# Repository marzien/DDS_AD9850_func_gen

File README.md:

# AD9850 DDS Function Generator (STM32F103)

Rotary-encoder controlled signal generator built from an AD9850 DDS module,
a 20x4 HD44780 LCD with PCF8574 I2C backpack and an STM32F103RB.

## Features
- 0 Hz – 40 MHz, 1 Hz resolution (125 MHz reference clock)
- STM32 runs at 72 MHz (8 MHz crystal × 9, APB1 36 MHz, 48 MHz USB clock)
- FreeRTOS V11.2.0 with four statically allocated tasks (no heap)
- Phase offset in 11.25° steps
- Output on/off (AD9850 power-down)
- Linear frequency sweep (up or down), period 0.1 s – 60 s
- Burst / gated output: on for X ms, off for Y ms (1 ms – 60 s each), also during a sweep
- Settings are saved to flash and restored at power-up
- Text command interface over the Blue Pill micro-USB port (USB virtual COM port)
- Outputs of the AD9850 module: **sine** on ZOUT1/ZOUT2, **square** on QOUT1/QOUT2
  (square duty cycle is set by the blue trimmer on the module). The AD9850 cannot
  generate triangle/sawtooth.

## Wiring
| STM32 | Function | Connect to |
|------|----------|------------|
| PA0  | W_CLK    | AD9850 W_CLK |
| PA1  | FQ_UD    | AD9850 FQ_UD |
| PA2  | Data     | AD9850 D7 (serial data) |
| –    | RESET    | AD9850 RESET → GND |
| PA6  | BTN_A    | Encoder A / CLK |
| PA4  | BTN_B    | Encoder B / DT |
| PA5  | BTN_PUSH | Encoder SW (to GND when pressed; internal pull-up + optional 10k to 3V3) |
| PB10 | I2C2 SCL | LCD backpack SCL |
| PB11 | I2C2 SDA | LCD backpack SDA |

Power the encoder from 3V3 (PA4/PA5/PA6 are not 5 V tolerant).
LCD address 0x27 or 0x3F is auto-detected (`SLAVE_ADDRESS_LCD` in `I2C_LCD.h`).

## Controls
**Main screen**
```
Freq:      1,000 Hz     <- cursor under the digit being changed
Step: 1 kHz
Phase: 0.00°
Output: ON
```
- Rotate: change frequency by the digit under the cursor
- Press and turn: change the step – clockwise = bigger, counter-clockwise = smaller
  (1 Hz … 10 MHz, shown on the "Step:" line and by the cursor)
- Short press: move cursor one digit left (1 Hz … 10 MHz, wraps)
- Long press: open menu
- While sweeping the screen shows live frequency, start, stop and period;
  short press stops the sweep

**Menu** (3 items visible, scrolls)
```
MENU      hold=exit
>Output           ON
 Phase         0.00°
 Sweep           OFF
```
Items: Output, Phase, Burst, On time, Off time, Sweep, Sw start, Sw stop, Sw time, Exit
- Rotate: select item / change value while editing (marker changes to `*`)
- Short press: edit / confirm (on frequency items it moves the digit cursor)
- Press and turn while editing Sw start / Sw stop: change the step
- Long press: confirm edit, or leave the menu

**Burst:** set Burst ON, then On time / Off time. The output is switched with the
AD9850 power-down bit, timed from SysTick (1 ms resolution). Each cycle starts with
the on time. Times change in 1 ms steps below 100 ms, 10 ms below 1 s, 100 ms below
10 s and 1 s above. The main screen shows `Burst on/off ms` on the last line (`Out:BST`
while sweeping). Gating is not synchronised to the waveform, so a burst does not start
or end at a zero crossing.

## Saved settings
All settings (frequency, step, phase, output, sweep start/stop/time, sweep on/off)
are saved to flash automatically 3 s after the last knob or button action, and
restored at power-up. Hold the encoder button while powering up to restore the
defaults (the splash screen shows "Defaults restored").

Storage uses the last 1 KB page of the first 64 KB (0x0800FC00), split into
32 slots, so the page is erased only once per 32 saves. For that reason the
linker script limits program flash to 63 KB.

LCD size is set by `LCD_COLS` / `LCD_ROWS` in `Core/Inc/I2C_LCD.h` (layout is designed for 20x4).

## USB command interface
Plug the Blue Pill micro-USB into a PC: it appears as a virtual COM port
("AD9850 DDS Function Generator", VID 0483 / PID 5740; Windows 10/11 needs no driver).
Open it with any terminal (PuTTY, Arduino serial monitor, Python `pyserial`); the baud rate
does not matter. One command per line, case-insensitive; every command answers `OK` or `ERR ...`.

| Command | Meaning |
|---|---|
| `F 1000`, `F 12.5k`, `F 7.1M` | set frequency (0 … 40 MHz), stops a running sweep |
| `STEP 1k` | encoder step, power of ten 1 … 10M |
| `PH 90` | phase in degrees (rounded to 11.25° steps) |
| `OUT ON` / `OUT OFF` | output on/off |
| `SWEEP 100 10k 2.5` | sweep 100 Hz → 10 kHz in 2.5 s and start it |
| `SWEEP ON` / `SWEEP OFF` | start/stop the sweep with the stored settings |
| `BURST 10 90` | burst: 10 ms on, 90 ms off, and start it |
| `BURST ON` / `BURST OFF` | burst mode on/off |
| `SAVE` | write settings to flash now (otherwise saved 3 s after the last change) |
| `?` or `STATUS` | print all settings |
| `*IDN?` | identification string |
| `MEM` | flash / RAM use and the minimum free stack of every task |
| `HELP` | list the commands |

Remote changes update the LCD and are autosaved like changes made with the knob.
Notes:
- Some Blue Pills have a 10 kΩ resistor (R10) on USB D+ instead of 1.5 kΩ. If the PC does
  not detect the board, add 1.8 kΩ between PA12 and 3.3 V (or replace R10 with 1.5 kΩ).
- The firmware pulls D+ low for 20 ms at start-up so the PC re-detects the board after a reset.
- With the carrier PCB, do not connect the PC USB and the 5 V DC jack at the same time
  (the PC would supply the whole board through the Blue Pill 5V pin).

## Firmware structure (FreeRTOS)
| Task | Priority | Stack | Job |
|---|---|---|---|
| DDS | 4 (highest) | 640 B | the only code that writes to the AD9850: applies settings, steps the sweep every 5 ms, runs the burst gate every 1 ms |
| INPUT | 3 | 512 B | samples the encoder and button every 1 ms, wakes the UI task |
| UI | 2 | 1536 B | menus, LCD, settings autosave to flash |
| USB | 1 | 1536 B | command parser, woken by the USB interrupt |
| IDLE | 0 | 384 B | FreeRTOS idle task |

- The UI and USB tasks share the settings under one mutex and hand them to the DDS task with
  `DDS_Configure()`. Because the DDS task has the highest priority, sweep and burst timing no
  longer depend on LCD redraws or USB traffic.
- FreeRTOS uses SysTick; the HAL time base runs on TIM4. The USB interrupt has priority 5
  (`configLIBRARY_MAX_SYSCALL_INTERRUPT_PRIORITY`), TIM4 / SysTick / PendSV priority 15.
- Everything is statically allocated (`configSUPPORT_DYNAMIC_ALLOCATION 0`), so RAM use is fixed
  at link time. Stack overflow checking (method 2) is on.
- The Debug configuration is built with `-Og` (was `-O0`) to keep flash use low.

### Memory budget
`python tools/mem_check.py` (after a build) prints flash / RAM use and a worst-case stack
estimate for every task from the call graph:

| | Used | Limit |
|---|---|---|
| Flash | 39.3 KB | 63 KB (61 %) |
| RAM (data + bss + heap + main stack) | 12.2 KB | 20 KB (59 %) |

| Stack | Size | Estimated need |
|---|---|---|
| DDS | 640 B | 192 B |
| INPUT | 512 B | 136 B |
| UI | 1536 B | 760 B |
| USB | 1536 B | 704 B |
| IDLE | 384 B | 64 B |
| Interrupts (main stack) | 1536 B | 504 B |

These are estimates; the USB command `MEM` reports the real minimum free stack on the board.

## Tuning
In `Core/Inc/Rotary_Sw.h`:
- `RS_STEPS_PER_DETENT` – 4 for KY-040 style encoders, 2 if one click counts double
- `RS_REVERSE` – flip rotation direction
- `RS_BTN_ACTIVE_LEVEL` – 0 (default) for a switch to GND, 1 for a switch to 3V3

## Building (STM32CubeIDE)
- File > Import > General > Existing Projects into Workspace, select this folder
  (project name `DDS_AD9850_FULL`), then build with the hammer icon.
- Startup code: `Core/Startup/startup_stm32f103rbtx.s`, linker script: `STM32F103RBTX_FLASH.ld`.
- Pin configuration lives in `DDS_AD9850_FULL.ioc` (toolchain: STM32CubeIDE). Application code is
  inside `USER CODE` blocks and in separate files, so it survives code regeneration.

## Hardware
A KiCad carrier PCB (Blue Pill + AD9850 module sockets, level shifter, LM7171 sine amplifier,
square buffer, sync output, BNC connectors) is in [`Hardware/`](Hardware/README.md).

## Source layout
- `Core/Src/AD9850.c` – DDS serial driver
- `Core/Src/I2C_LCD.c` – LCD driver
- `Core/Src/Rotary_Sw.c` – encoder + button, polled by the INPUT task (1 ms)
- `Core/Src/App.c` – task creation, settings mutex, memory report, RTOS hooks
- `Core/Src/Dds.c` – DDS task: output, sweep and burst timing
- `Core/Src/FuncGen.c` – UI task: menus, LCD, settings
- `Core/Src/Flash_Store.c` – wear-levelled settings storage in flash
- `Core/Src/UsbCmd.c` – USB task: command parser
- `Core/Inc/FreeRTOSConfig.h` – kernel configuration
- `Middlewares/Third_Party/FreeRTOS/` – FreeRTOS kernel V11.2.0 (tasks, queue, list, ARM_CM3 port)
- `tools/mem_check.py` – flash / RAM / stack budget check
- `USB_DEVICE/` – USB CDC device glue (descriptors, low-level driver, virtual COM port)
- `Middlewares/ST/STM32_USB_Device_Library/` – ST USB device library v2.11.6 (core + CDC)

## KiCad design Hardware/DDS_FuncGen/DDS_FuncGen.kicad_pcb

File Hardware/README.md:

# Carrier PCB (KiCad 10)

100 × 90 mm, 2-layer board that carries the Blue Pill and the AD9850 module on
female headers, plus the output stage.

## What is on the board
- **Blue Pill** socket (2 × 1×20 female headers, rows 15.24 mm apart, USB towards the left edge).
- **AD9850 module (HC-SR08)** socket (2 × 1×10 female headers).
- **74AHCT125** level shifter: PA0/PA1/PA2/PA3 → W_CLK/FQ_UD/DATA/RESET. The STM32's 3.3 V
  logic is below the AD9850's 3.5 V input-high minimum at 5 V supply, so the buffer makes it reliable.
  RESET is driven by PA3; R1 keeps it low (the current firmware leaves PA3 as an input).
- Data row of the module: D2…D6 tied to GND (guarantees serial mode). VCC, D7 and GND
  of that row are deliberately **not connected**, because some modules have D7 and GND swapped.
- **Sine output (J4, BNC)**: ZOUT2 → 22 µF + 100 nF AC coupling (centres the sine on 0 V) →
  1 k amplitude pot RV1 → LM7171, gain 4 → 49.9 Ω → BNC.
- **Square output (J5, BNC)**: QOUT1 → 74LVC1G17 buffer → 68 Ω → BNC (0–5 V into high-Z).
- **Sync output (J6, BNC)**: PB0 → 100 Ω (needs the sync firmware feature).
- **Power**: 5 V DC jack (2.1 mm, centre +) → SS34 reverse protection → +5V.
  A0515S-2WR3 isolated DC-DC → LC filter → 78L12 / 79L12 → ±12 V for the LM7171.
- Headers: **J2** LCD (GND, VCC, SDA, SCL), **J3** KY-040 (CLK, DT, SW, +, GND), R8 = 10 k SW pull-up.
- 4 × M3 mounting holes.

## Check before ordering
1. **AD9850 module row spacing**: set to 20.32 mm (`AD9850_ROW_SPACING` in `tools/design.py`).
   The seller drawing says "20 mm" – measure your module.
2. **Blue Pill orientation**: with USB on the left, the top row must read
   `G G 3.3 R B11 B10 … A0 C15 C14 C13 VB`. The silkscreen shows every pin name – compare with your board.
3. Power the board from the DC jack **or** the Blue Pill USB, not from both at the same time.

## Files
| Path | Content |
|---|---|
| `DDS_FuncGen/DDS_FuncGen.kicad_pro` | KiCad project (open this) |
| `DDS_FuncGen/production/DDS_FuncGen_gerbers_JLCPCB.zip` | Gerbers + drill, ready to upload |
| `DDS_FuncGen/production/DDS_FuncGen_BOM.csv` | Bill of materials |
| `DDS_FuncGen/production/DDS_FuncGen_schematic.pdf` | Schematic |
| `DDS_FuncGen/production/erc.rpt`, `drc.rpt` | 0 ERC errors, 0 DRC violations, 0 unconnected |
| `tools/design.py` | Parts, nets and positions (single source) |
| `tools/gen_project.py` | Generates libraries, schematic and PCB from `design.py` |
| `tools/route.py` | Autoroutes with Freerouting and adds GND planes |

## Regenerating
```
"%LOCALAPPDATA%\Programs\KiCad\10.0\bin\python.exe" tools\gen_project.py
"%LOCALAPPDATA%\Programs\KiCad\10.0\bin\python.exe" tools\route.py <freerouting-2.1.0.jar> <java.exe>
```
`gen_project.py --sch-only` rewrites only the schematic and libraries, leaving the routed PCB alone.
Freerouting 2.1.0 runs on Java 21 (the JRE bundled with STM32CubeIDE works).

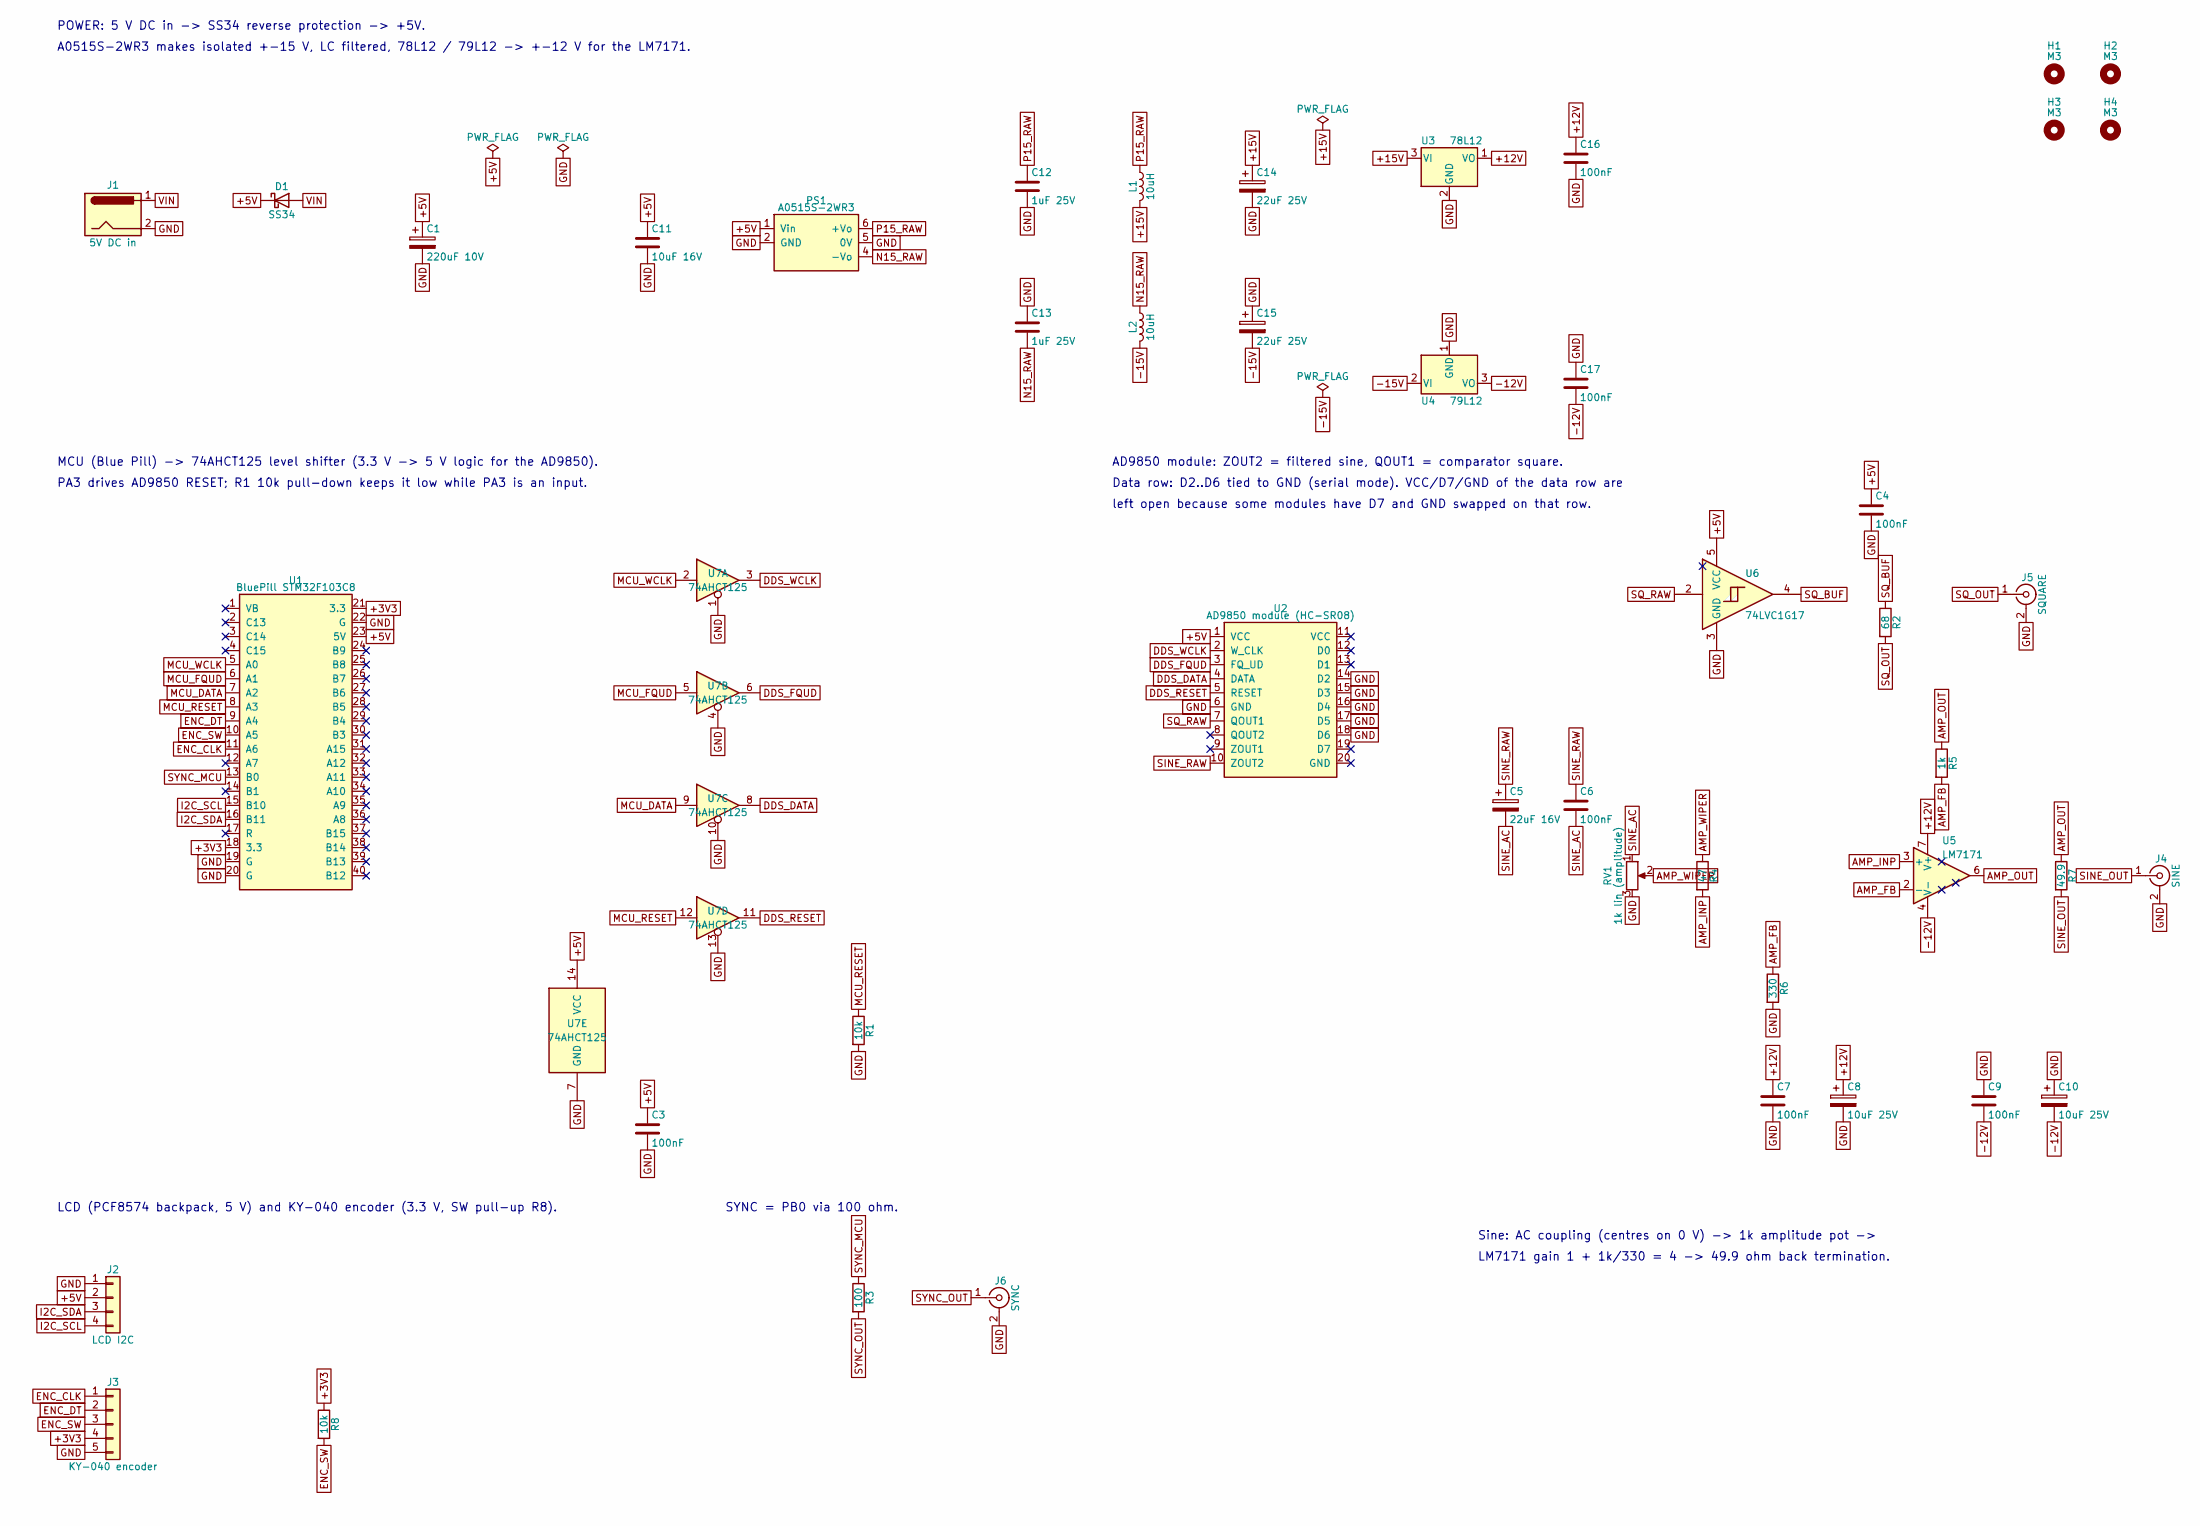
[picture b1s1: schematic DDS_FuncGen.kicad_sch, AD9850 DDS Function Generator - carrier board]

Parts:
C1: 220uF 10V; CP_Radial_D8.0mm_P3.50mm
C3, C4, C6, C7, C9, C16, C17: 100nF; C_0805_2012Metric_Pad1.18x1.45mm_HandSolder
C5: 22uF 16V; CP_Radial_D5.0mm_P2.00mm
C8, C10: 10uF 25V; CP_Radial_D5.0mm_P2.00mm
C11: 10uF 16V; C_0805_2012Metric_Pad1.18x1.45mm_HandSolder
C12, C13: 1uF 25V; C_0805_2012Metric_Pad1.18x1.45mm_HandSolder
C14, C15: 22uF 25V; CP_Radial_D5.0mm_P2.00mm
D1: SS34; D_SMA_Handsoldering
H1, H2, H3, H4: M3; MountingHole_3.2mm_M3
J1: 5V DC in; BarrelJack_Horizontal
J2: LCD I2C; PinHeader_1x04_P2.54mm_Vertical
J3: KY-040 encoder; PinHeader_1x05_P2.54mm_Vertical
J4: SINE; BNC_TEConnectivity_1478035_Horizontal
J5: SQUARE; BNC_TEConnectivity_1478035_Horizontal
J6: SYNC; BNC_TEConnectivity_1478035_Horizontal
L1, L2: 10uH; L_1210_3225Metric_Pad1.42x2.65mm_HandSolder
PS1: A0515S-2WR3; Mornsun_SIP6_A_S-2WR3
R1, R8: 10k; R_0805_2012Metric_Pad1.20x1.40mm_HandSolder
R2: 68; R_0805_2012Metric_Pad1.20x1.40mm_HandSolder
R3: 100; R_0805_2012Metric_Pad1.20x1.40mm_HandSolder
R4: 47; R_0805_2012Metric_Pad1.20x1.40mm_HandSolder
R5: 1k; R_0805_2012Metric_Pad1.20x1.40mm_HandSolder
R6: 330; R_0805_2012Metric_Pad1.20x1.40mm_HandSolder
R7: 49.9; R_0805_2012Metric_Pad1.20x1.40mm_HandSolder
RV1: 1k lin (amplitude); Potentiometer_Alps_RK09K_Single_Vertical
U1: BluePill STM32F103C8; BluePill_Socket
U2: AD9850 module (HC-SR08); AD9850_Module_Socket
U3: 78L12; TO-92_Inline
U4: 79L12; TO-92_Inline
U5: LM7171; SOIC-8_3.9x4.9mm_P1.27mm
U6: 74LVC1G17; SOT-23-5_HandSoldering
U7: 74AHCT125; SOIC-14_3.9x8.7mm_P1.27mm

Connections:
+3V3: J3.4, R8.1, U1.18 (3.3), U1.21 (3.3)
+5V: C1.1, C3.1, C4.1, C11.1, D1.1 (K), J2.2, PS1.1 (Vin), U1.23 (5V), U2.1 (VCC), U6.5 (VCC), U7.14 (VCC)
+12V: C7.1, C8.1, C16.1, U3.1 (VO), U5.7 (V+)
+15V: C14.1, L1.2, U3.3 (VI)
-12V: C9.2, C10.2, C17.2, U4.3 (VO), U5.4 (V-)
-15V: C15.2, L2.2, U4.2 (VI)
AMP_FB: R5.2, R6.1, U5.2 (-)
AMP_INP: R4.2, U5.3 (+)
AMP_OUT: R5.1, R7.1, U5.6
AMP_WIPER: R4.1, RV1.2
DDS_DATA: U2.4 (DATA), U7.8
DDS_FQUD: U2.3 (FQ_UD), U7.6
DDS_RESET: U2.5 (RESET), U7.11
DDS_WCLK: U2.2 (W_CLK), U7.3
ENC_CLK: J3.1, U1.11 (A6)
ENC_DT: J3.2, U1.9 (A4)
ENC_SW: J3.3, R8.2, U1.10 (A5)
GND: C1.2, C3.2, C4.2, C7.2, C8.2, C9.1, C10.1, C11.2, C12.2, C13.1, C14.2, C15.1, C16.2, C17.1, J1.2, J2.1, J3.5, J4.2 (Ext), J5.2 (Ext), J6.2 (Ext), PS1.2 (GND), PS1.5 (0V), R1.2, R6.2, RV1.3, U1.19 (G), U1.20 (G), U1.22 (G), U2.6 (GND), U2.14 (D2), U2.15 (D3), U2.16 (D4), U2.17 (D5), U2.18 (D6), U3.2 (GND), U4.1 (GND), U6.3 (GND), U7.1, U7.4, U7.7 (GND), U7.10, U7.13
I2C_SCL: J2.4, U1.15 (B10)
I2C_SDA: J2.3, U1.16 (B11)
MCU_DATA: U1.7 (A2), U7.9
MCU_FQUD: U1.6 (A1), U7.5
MCU_RESET: R1.1, U1.8 (A3), U7.12
MCU_WCLK: U1.5 (A0), U7.2
N15_RAW: C13.2, L2.1, PS1.4 (-Vo)
P15_RAW: C12.1, L1.1, PS1.6 (+Vo)
SINE_AC: C5.2, C6.2, RV1.1
SINE_OUT: J4.1 (In), R7.2
SINE_RAW: C5.1, C6.1, U2.10 (ZOUT2)
SQ_BUF: R2.1, U6.4
SQ_OUT: J5.1 (In), R2.2
SQ_RAW: U2.7 (QOUT1), U6.2
SYNC_MCU: R3.1, U1.13 (B0)
SYNC_OUT: J6.1 (In), R3.2
VIN: D1.2 (A), J1.1

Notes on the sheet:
POWER: 5 V DC in -> SS34 reverse protection -> +5V.
A0515S-2WR3 makes isolated +-15 V, LC filtered, 78L12 / 79L12 -> +-12 V for the LM7171.
MCU (Blue Pill) -> 74AHCT125 level shifter (3.3 V -> 5 V logic for the AD9850).
PA3 drives AD9850 RESET; R1 10k pull-down keeps it low while PA3 is an input.
AD9850 module: ZOUT2 = filtered sine, QOUT1 = comparator square.
Data row: D2..D6 tied to GND (serial mode). VCC/D7/GND of the data row are
left open because some modules have D7 and GND swapped on that row.
Sine: AC coupling (centres on 0 V) -> 1k amplitude pot ->
LM7171 gain 1 + 1k/330 = 4 -> 49.9 ohm back termination.
LCD (PCF8574 backpack, 5 V) and KY-040 encoder (3.3 V, SW pull-up R8).
SYNC = PB0 via 100 ohm.

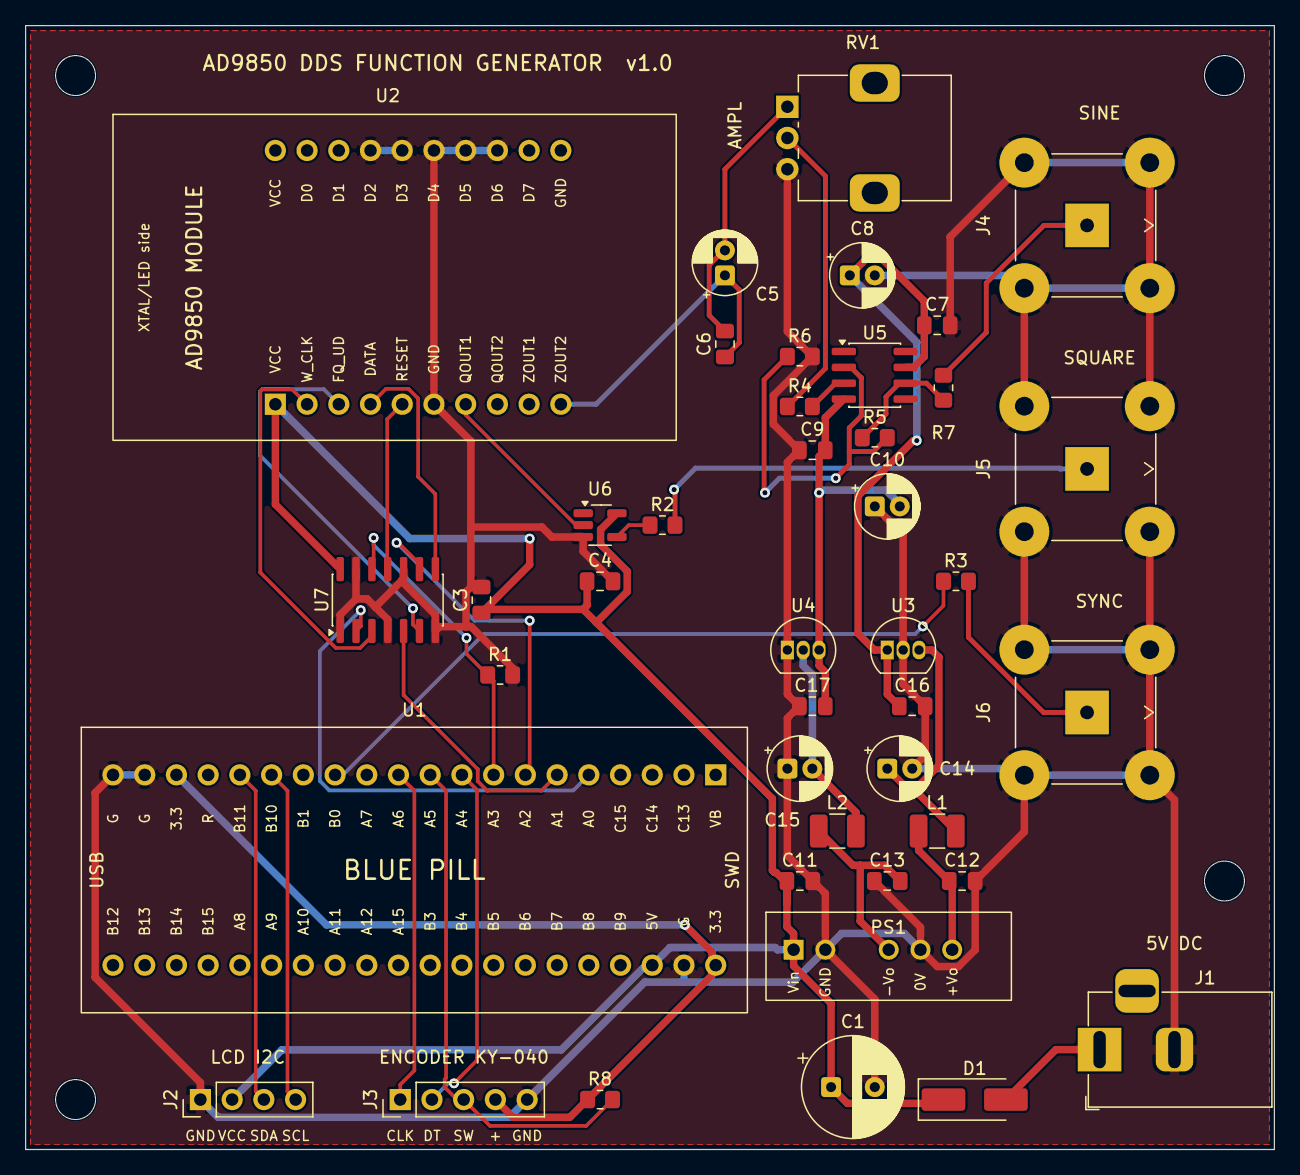
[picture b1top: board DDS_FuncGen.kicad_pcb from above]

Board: 2 copper layers, 100.0 x 90.0 mm, 46 parts (0 on the bottom side), 35 nets.

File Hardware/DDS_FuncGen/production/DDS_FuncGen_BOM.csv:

"Refs","Value","Footprint","Qty"
"C1","220uF 10V","Capacitor_THT:CP_Radial_D8.0mm_P3.50mm","1"
"C3,C4,C6,C7,C9,C16,C17","100nF","Capacitor_SMD:C_0805_2012Metric_Pad1.18x1.45mm_HandSolder","7"
"C5","22uF 16V","Capacitor_THT:CP_Radial_D5.0mm_P2.00mm","1"
"C8,C10","10uF 25V","Capacitor_THT:CP_Radial_D5.0mm_P2.00mm","2"
"C11","10uF 16V","Capacitor_SMD:C_0805_2012Metric_Pad1.18x1.45mm_HandSolder","1"
"C12,C13","1uF 25V","Capacitor_SMD:C_0805_2012Metric_Pad1.18x1.45mm_HandSolder","2"
"C14,C15","22uF 25V","Capacitor_THT:CP_Radial_D5.0mm_P2.00mm","2"
"D1","SS34","Diode_SMD:D_SMA_Handsoldering","1"
"J1","5V DC in","Connector_BarrelJack:BarrelJack_Horizontal","1"
"J2","LCD I2C","Connector_PinHeader_2.54mm:PinHeader_1x04_P2.54mm_Vertical","1"
"J3","KY-040 encoder","Connector_PinHeader_2.54mm:PinHeader_1x05_P2.54mm_Vertical","1"
"J4","SINE","Connector_Coaxial:BNC_TEConnectivity_1478035_Horizontal","1"
"J5","SQUARE","Connector_Coaxial:BNC_TEConnectivity_1478035_Horizontal","1"
"J6","SYNC","Connector_Coaxial:BNC_TEConnectivity_1478035_Horizontal","1"
"L1,L2","10uH","Inductor_SMD:L_1210_3225Metric_Pad1.42x2.65mm_HandSolder","2"
"PS1","A0515S-2WR3","DDS_FuncGen:Mornsun_SIP6_A_S-2WR3","1"
"R1,R8","10k","Resistor_SMD:R_0805_2012Metric_Pad1.20x1.40mm_HandSolder","2"
"R2","68","Resistor_SMD:R_0805_2012Metric_Pad1.20x1.40mm_HandSolder","1"
"R3","100","Resistor_SMD:R_0805_2012Metric_Pad1.20x1.40mm_HandSolder","1"
"R4","47","Resistor_SMD:R_0805_2012Metric_Pad1.20x1.40mm_HandSolder","1"
"R5","1k","Resistor_SMD:R_0805_2012Metric_Pad1.20x1.40mm_HandSolder","1"
"R6","330","Resistor_SMD:R_0805_2012Metric_Pad1.20x1.40mm_HandSolder","1"
"R7","49.9","Resistor_SMD:R_0805_2012Metric_Pad1.20x1.40mm_HandSolder","1"
"RV1","1k lin (amplitude)","Potentiometer_THT:Potentiometer_Alps_RK09K_Single_Vertical","1"
"U1","BluePill STM32F103C8","DDS_FuncGen:BluePill_Socket","1"
"U2","AD9850 module (HC-SR08)","DDS_FuncGen:AD9850_Module_Socket","1"
"U3","78L12","Package_TO_SOT_THT:TO-92_Inline","1"
"U4","79L12","Package_TO_SOT_THT:TO-92_Inline","1"
"U5","LM7171","Package_SO:SOIC-8_3.9x4.9mm_P1.27mm","1"
"U6","74LVC1G17","Package_TO_SOT_SMD:SOT-23-5_HandSoldering","1"
"U7","74AHCT125","Package_SO:SOIC-14_3.9x8.7mm_P1.27mm","1"

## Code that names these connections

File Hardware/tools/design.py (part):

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            '16': 'D4', '17': 'D5', '18': 'D6', '19': 'D7', '20': 'GND'}
# Data row: only D2..D6 tied low (serial mode needs D2=0). VCC, D7 and GND of the
# data row are left open: some modules have D7 and GND swapped on that row.
AD_PINS = {'1': '+5V', '2': 'DDS_WCLK', '3': 'DDS_FQUD', '4': 'DDS_DATA',
           '5': 'DDS_RESET', '6': 'GND', '7': 'SQ_RAW', '8': None, '9': None,
           '10': 'SINE_RAW', '11': None, '12': None, '13': None, '14': 'GND',
           '15': 'GND', '16': 'GND', '17': 'GND', '18': 'GND', '19': None, '20': None}
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    dict(ref='FLG2', lib='power:PWR_FLAG', value='PWR_FLAG', fp=None, pins={'1': 'GND'}, sch=(111.76, 45.72)),
    # ---- isolated +-15 V -> +-12 V for the amplifier
    dict(ref='PS1', lib=KLIB + ':A0515S-2WR3', value='A0515S-2WR3', fp=KLIB + ':Mornsun_SIP6_A_S-2WR3',
         pins={'1': '+5V', '2': 'GND', '4': 'N15_RAW', '5': 'GND', '6': 'P15_RAW'},
         sch=(157.48, 60.96), pcb=(61.5, 74.0, 0)),
    dict(ref='C11', lib='Device:C', value='10uF 16V', fp=C0805,
         pins={'1': '+5V', '2': 'GND'}, sch=(127.0, 60.96), pcb=(62.0, 68.5, 0)),
    dict(ref='C12', lib='Device:C', value='1uF 25V', fp=C0805,
         pins={'1': 'P15_RAW', '2': 'GND'}, sch=(195.58, 50.8), pcb=(75.0, 68.5, 0)),
    dict(ref='C13', lib='Device:C', value='1uF 25V', fp=C0805,
         pins={'1': 'GND', '2': 'N15_RAW'}, sch=(195.58, 76.2), pcb=(69.0, 68.5, 0)),
    dict(ref='L1', lib='Device:L', value='10uH', fp='Inductor_SMD:L_1210_3225Metric_Pad1.42x2.65mm_HandSolder',
         pins={'1': 'P15_RAW', '2': '+15V'}, sch=(215.9, 50.8), pcb=(73.0, 64.5, 0)),
    dict(ref='L2', lib='Device:L', value='10uH', fp='Inductor_SMD:L_1210_3225Metric_Pad1.42x2.65mm_HandSolder',
         pins={'1': 'N15_RAW', '2': '-15V'}, sch=(215.9, 76.2), pcb=(65.0, 64.5, 0)),
    dict(ref='C14', lib='Device:C_Polarized', value='22uF 25V', fp=CP5,
         pins={'1': '+15V', '2': 'GND'}, sch=(236.22, 50.8), pcb=(69.0, 59.5, 0)),
    dict(ref='C15', lib='Device:C_Polarized', value='22uF 25V', fp=CP5,
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    dict(ref='U1', lib=KLIB + ':BluePill', value='BluePill STM32F103C8', fp=KLIB + ':BluePill_Socket',
         pins=BP_PINS, sch=(63.5, 152.4), pcb=(7.0, 60.0, 0)),
    dict(ref='U7', lib='74xx:74AHCT125', value='74AHCT125', fp='Package_SO:SOIC-14_3.9x8.7mm_P1.27mm',
         pins={'1': 'GND', '2': 'MCU_WCLK', '3': 'DDS_WCLK', '4': 'GND', '5': 'MCU_FQUD', '6': 'DDS_FQUD',
               '7': 'GND', '8': 'DDS_DATA', '9': 'MCU_DATA', '10': 'GND', '11': 'DDS_RESET',
               '12': 'MCU_RESET', '13': 'GND', '14': '+5V'},
         sch={1: (139.7, 121.92), 2: (139.7, 142.24), 3: (139.7, 162.56), 4: (139.7, 182.88), 5: (114.3, 203.2)},
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    dict(ref='C3', lib='Device:C', value='100nF', fp=C0805,
         pins={'1': '+5V', '2': 'GND'}, sch=(127.0, 220.98), pcb=(36.5, 46.0, 90)),
    dict(ref='R1', lib='Device:R', value='10k', fp=R0805,
         pins={'1': 'MCU_RESET', '2': 'GND'}, sch=(165.1, 203.2), pcb=(38.0, 52.0, 0)),

    # ---- AD9850 module
    dict(ref='U2', lib=KLIB + ':AD9850_Module', value='AD9850 module (HC-SR08)', fp=KLIB + ':AD9850_Module_Socket',
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
    # ---- square output buffer
    dict(ref='U6', lib='74xGxx:74LVC1G17', value='74LVC1G17', fp='Package_TO_SOT_SMD:SOT-23-5_HandSoldering',
         pins={'1': None, '2': 'SQ_RAW', '3': 'GND', '4': 'SQ_BUF', '5': '+5V'},
         sch=(325.12, 124.46), pcb=(46.0, 40.0, 0)),
    dict(ref='C4', lib='Device:C', value='100nF', fp=C0805,
         pins={'1': '+5V', '2': 'GND'}, sch=(347.98, 109.22), pcb=(46.0, 44.5, 0)),
    dict(ref='R2', lib='Device:R', value='68', fp=R0805,
         pins={'1': 'SQ_BUF', '2': 'SQ_OUT'}, sch=(350.52, 129.54), pcb=(51.0, 40.0, 0)),
    dict(ref='J5', lib='Connector:Conn_Coaxial', value='SQUARE', fp=BNC,
         pins={'1': 'SQ_OUT', '2': 'GND'}, sch=(375.92, 124.46), pcb=(85.0, 35.5, -90)),

    # ---- sine: AC coupling, amplitude pot, LM7171 x4 amplifier
    dict(ref='C5', lib='Device:C_Polarized', value='22uF 16V', fp=CP5,
         pins={'1': 'SINE_RAW', '2': 'SINE_AC'}, sch=(281.94, 162.56), pcb=(56.0, 20.0, 90)),
    dict(ref='C6', lib='Device:C', value='100nF', fp=C0805,
         pins={'1': 'SINE_RAW', '2': 'SINE_AC'}, sch=(294.64, 162.56), pcb=(56.0, 25.5, 90)),
    dict(ref='RV1', lib='Device:R_Potentiometer', value='1k lin (amplitude)', fp='Potentiometer_THT:Potentiometer_Alps_RK09K_Single_Vertical',
         pins={'1': 'SINE_AC', '2': 'AMP_WIPER', '3': 'GND'}, sch=(304.8, 175.26), pcb=(61.0, 6.5, 0)),
    dict(ref='R4', lib='Device:R', value='47', fp=R0805,
         pins={'1': 'AMP_WIPER', '2': 'AMP_INP'}, sch=(317.5, 175.26), pcb=(62.0, 30.5, 0)),
    dict(ref='U5', lib='Amplifier_Operational:LM7171xIM', value='LM7171', fp='Package_SO:SOIC-8_3.9x4.9mm_P1.27mm',
         pins={'1': None, '2': 'AMP_FB', '3': 'AMP_INP', '4': '-12V', '5': None, '6': 'AMP_OUT', '7': '+12V', '8': None},
         sch=(360.68, 175.26), pcb=(68.0, 28.0, 0)),
    dict(ref='R5', lib='Device:R', value='1k', fp=R0805,
         pins={'1': 'AMP_OUT', '2': 'AMP_FB'}, sch=(360.68, 154.94), pcb=(68.0, 33.0, 0)),
    dict(ref='R6', lib='Device:R', value='330', fp=R0805,
         pins={'1': 'AMP_FB', '2': 'GND'}, sch=(330.2, 195.58), pcb=(62.0, 26.5, 0)),
    dict(ref='R7', lib='Device:R', value='49.9', fp=R0805,
         pins={'1': 'AMP_OUT', '2': 'SINE_OUT'}, sch=(382.54, 175.26), pcb=(73.5, 29.0, 90)),
    dict(ref='J4', lib='Connector:Conn_Coaxial', value='SINE', fp=BNC,
         pins={'1': 'SINE_OUT', '2': 'GND'}, sch=(400.05, 175.26), pcb=(85.0, 16.0, -90)),
    dict(ref='C7', lib='Device:C', value='100nF', fp=C0805,
         pins={'1': '+12V', '2': 'GND'}, sch=(330.2, 215.9), pcb=(73.0, 24.0, 0)),
    dict(ref='C8', lib='Device:C_Polarized', value='10uF 25V', fp=CP5,
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
    # ---- sync output
    dict(ref='R3', lib='Device:R', value='100', fp=R0805,
         pins={'1': 'SYNC_MCU', '2': 'SYNC_OUT'}, sch=(165.1, 251.46), pcb=(74.5, 44.5, 0)),
    dict(ref='J6', lib='Connector:Conn_Coaxial', value='SYNC', fp=BNC,
         pins={'1': 'SYNC_OUT', '2': 'GND'}, sch=(190.5, 251.46), pcb=(85.0, 55.0, -90)),

    # ---- LCD and encoder headers
    dict(ref='J2', lib='Connector_Generic:Conn_01x04', value='LCD I2C', fp='Connector_PinHeader_2.54mm:PinHeader_1x04_P2.54mm_Vertical',
         pins={'1': 'GND', '2': '+5V', '3': 'I2C_SDA', '4': 'I2C_SCL'}, sch=(30.48, 251.46), pcb=(14.0, 86.0, 90)),
    dict(ref='J3', lib='Connector_Generic:Conn_01x05', value='KY-040 encoder', fp='Connector_PinHeader_2.54mm:PinHeader_1x05_P2.54mm_Vertical',
         pins={'1': 'ENC_CLK', '2': 'ENC_DT', '3': 'ENC_SW', '4': '+3V3', '5': 'GND'}, sch=(30.48, 274.32), pcb=(30.0, 86.0, 90)),
    dict(ref='R8', lib='Device:R', value='10k', fp=R0805,
         pins={'1': '+3V3', '2': 'ENC_SW'}, sch=(68.58, 274.32), pcb=(46.0, 86.0, 0)),

    # ---- mounting holes
    dict(ref='H1', lib='Mechanical:MountingHole', value='M3', fp='MountingHole:MountingHole_3.2mm_M3', pins={}, sch=(381.0, 30.48), pcb=(4.0, 4.0, 0)),
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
